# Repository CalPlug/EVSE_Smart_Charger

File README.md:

# EVSE Smart Charger

By: Andy Begey, Brandon Metcalf, Luis Contreras, Shermaine Dayot, Omair Farooqui, Krishan Solanki, Alex Ramirez, Emon Sahaba

Project Managers: Dr. Michael Klopfer, Prof. GP Li. 

University of California, Irvine - California Institute for Telecommunications and Information Technology (Calit2)  

---
Example ESP32-WROOM-32 application demo: operation of Electric Vehicle Supply Equipment (EVSE) Smart Charger that connects to the internet and MQTT server which will allow EV owners to control the charging schedules and monitor power consumption. Uses Smartenit MQTT format. 

Example Application note for ESP32-WROOM-32

Copyright © The Regents of the Univeristy of California, 2018-19

Released into the public domain.

# Installation
Required tasks needed for the project: 

1. Install Arduino ESP32 on Windows using this link: https://github.com/espressif/arduino-esp32/blob/master/docs/arduino-ide/windows.md

2. Open Arduino IDE. Click File->Open, then navigate to the following path:    
`EVSE code/Arduino/Current_Year_DevelopmentFirmware/EVChargerESP32RTOS`

3. Open `EVChargerESP32RTOS.ino`. The .ino file and the accompanying libraries should open in the IDE.

4. Use the library "esp32-hal-spi.h" for SPI. Can be obtained from doing the first task. 

5. Set the board to `ESP32 Dev Module`.

# Building 
After following the steps for installation, you can start by creating an account on your desired MQTT broker for testing purposes. It comes in many types of flavors, but our personal favorite and recommendation is CloudMQTT. Go to this link: https://www.cloudmqtt.com/. After you have created your account, prepare to gather the MQTT user, password, port and server because you need these in order to connect with your server. You also need to prepare your desired network name and password. It is very important to note that the ESP32 is itself an access point initally and that you would need to create its own server where the user can input their own MQTT server and Network for the ESP32 to connect to. In the initial stages of testing your software without implementing the ESP32 as its own access point, you would need to hardcode the information you have gathered in the beginning. 

# Background of Operation 

The Smart Charger initializes inputs and safety checks. After the safety check passes, it tries to connect to the wifi available. Then after being connected to the wifi it connects to the mqtt server. Initially the charger is in state A which means it is not plugged in. When it is plugged in but not charging, the charger is in state B. The wattmeter reads values such as Vrms, Irms, and active power. When it changes to state C which is at charging state, both relays will turn on. Pressing the button at certain amount of times will turn off the load, change the load, reset, and enter AP mode.  

# Usage
Smart Charger can be used to monitor the charging conditions of an electric vehicle. Online, an EV owner will be able to have control over the charger, for example they may ask for voltage levels and will be able to change the load going into the vehicle. It will be very useful in time as the number of electric vehicle users increase.  

## Connecting to WiFi

Upon first boot and after resets, the EVSE Smart Charger will start an access point (AP) to allow user to connect to a certain WiFI Access Point and MQTT broker.

1. On another device, connect to AP with SSID: `EVSESetup9B25B2`.
2. On a web browser, navigate to `192.168.10.10`.
3. Enter your valid WiFi and MQTT credentials on the form displayed. Then click 'Save.'
4. A success message should appear, the EVSE AP should disconnect, then the EVSE should connect to the WiFI network specified.

If there a failure, reset the EVSE networking information by pressing the reset button 11-12 times.

## MQTT Commands

The EVSE unit can be controlled remotely via MQTT commands.

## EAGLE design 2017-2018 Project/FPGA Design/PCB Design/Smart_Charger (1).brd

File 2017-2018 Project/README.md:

# EV_Smart_Charger
---
Example ESP32-WROOM-32 application demo: operation of Electric Vehicle Supply Equipment (EVSE) Smart Charger that connects to the internet and MQTT server which will allow EV owners to control the charging schedules and monitor power consumption. Uses Smartenit MQTT format. 

Example Application note for ESP32-WROOM-32

Created by Andy Begey, Brandon Metcalf, Luis Contreras, Shermaine Dayot 

Project Managers: Dr. Michael Klopfer, Prof. GP Li. 

University of California, Irvine - California Institute for Telecommunications and Information Technology (Calit2)  

Copyright (C) The Regents of the Univeristy of California, 2018

Released into the public domain.

# Installation
---
Required tasks needed for the project: 

1.) Install Arduino ESP32 on Windows using this link: https://github.com/espressif/arduino-esp32/blob/master/docs/arduino-ide/windows.md

2.) Install ADE7953-Wattmeter-master into Arduino library which can be found in the EVSE_Smart_Charger github. 
    Go to: EVSE code->Arduino->libraries->ADE7953-Wattmeter-master for ESP32.

3.) Use the library "esp32-hal-spi.h" for SPI. Can be obtained from doing the first task. 

# Building 
---
After following the steps for installation, you can start by creating an account on your desired MQTT broker for testing purposes. It comes in many types of flavors, but our personal favorite and recommendation is CloudMQTT. Go to this link: https://www.cloudmqtt.com/. After you have created your account, prepare to gather the mqtt user, password, port and server because you need these in order to connect with your server. You also need to prepare your desired network name and password. It is very important to note that the ESP32 is itself an access point initally and that you would need to create its own server where the user can input their own MQTT server and Network for the ESP32 to connect to. In the initial stages of testing your software without implementing the ESP32 as its own access point, you would need to hardcode the information you have gathered in the beginning. 

# Background of Operation 
---
The Smart Charger initializes inputs and safety checks. After the safety check passes, it tries to connect to the wifi available. Then after being connected to the wifi it connects to the mqtt server. Initially the charger is in state A which means it is not plugged in. When it is plugged in but not charging, the charger is in state B. The wattmeter reads values such as Vrms, Irms, and active power. When it changes to state C which is at charging state, both relays will turn on. Pressing the button at certain amount of times will turn off the load, change the load, reset, and enter AP mode.  

# Usage
---
Smart Charger can be used to monitor the charging conditions of an electric vehicle. Online, an EV owner will be able to have control over the charger, for example they may ask for voltage levels and will be able to change the load going into the vehicle. It will be very useful in time as the number of electric vehicle users increase.

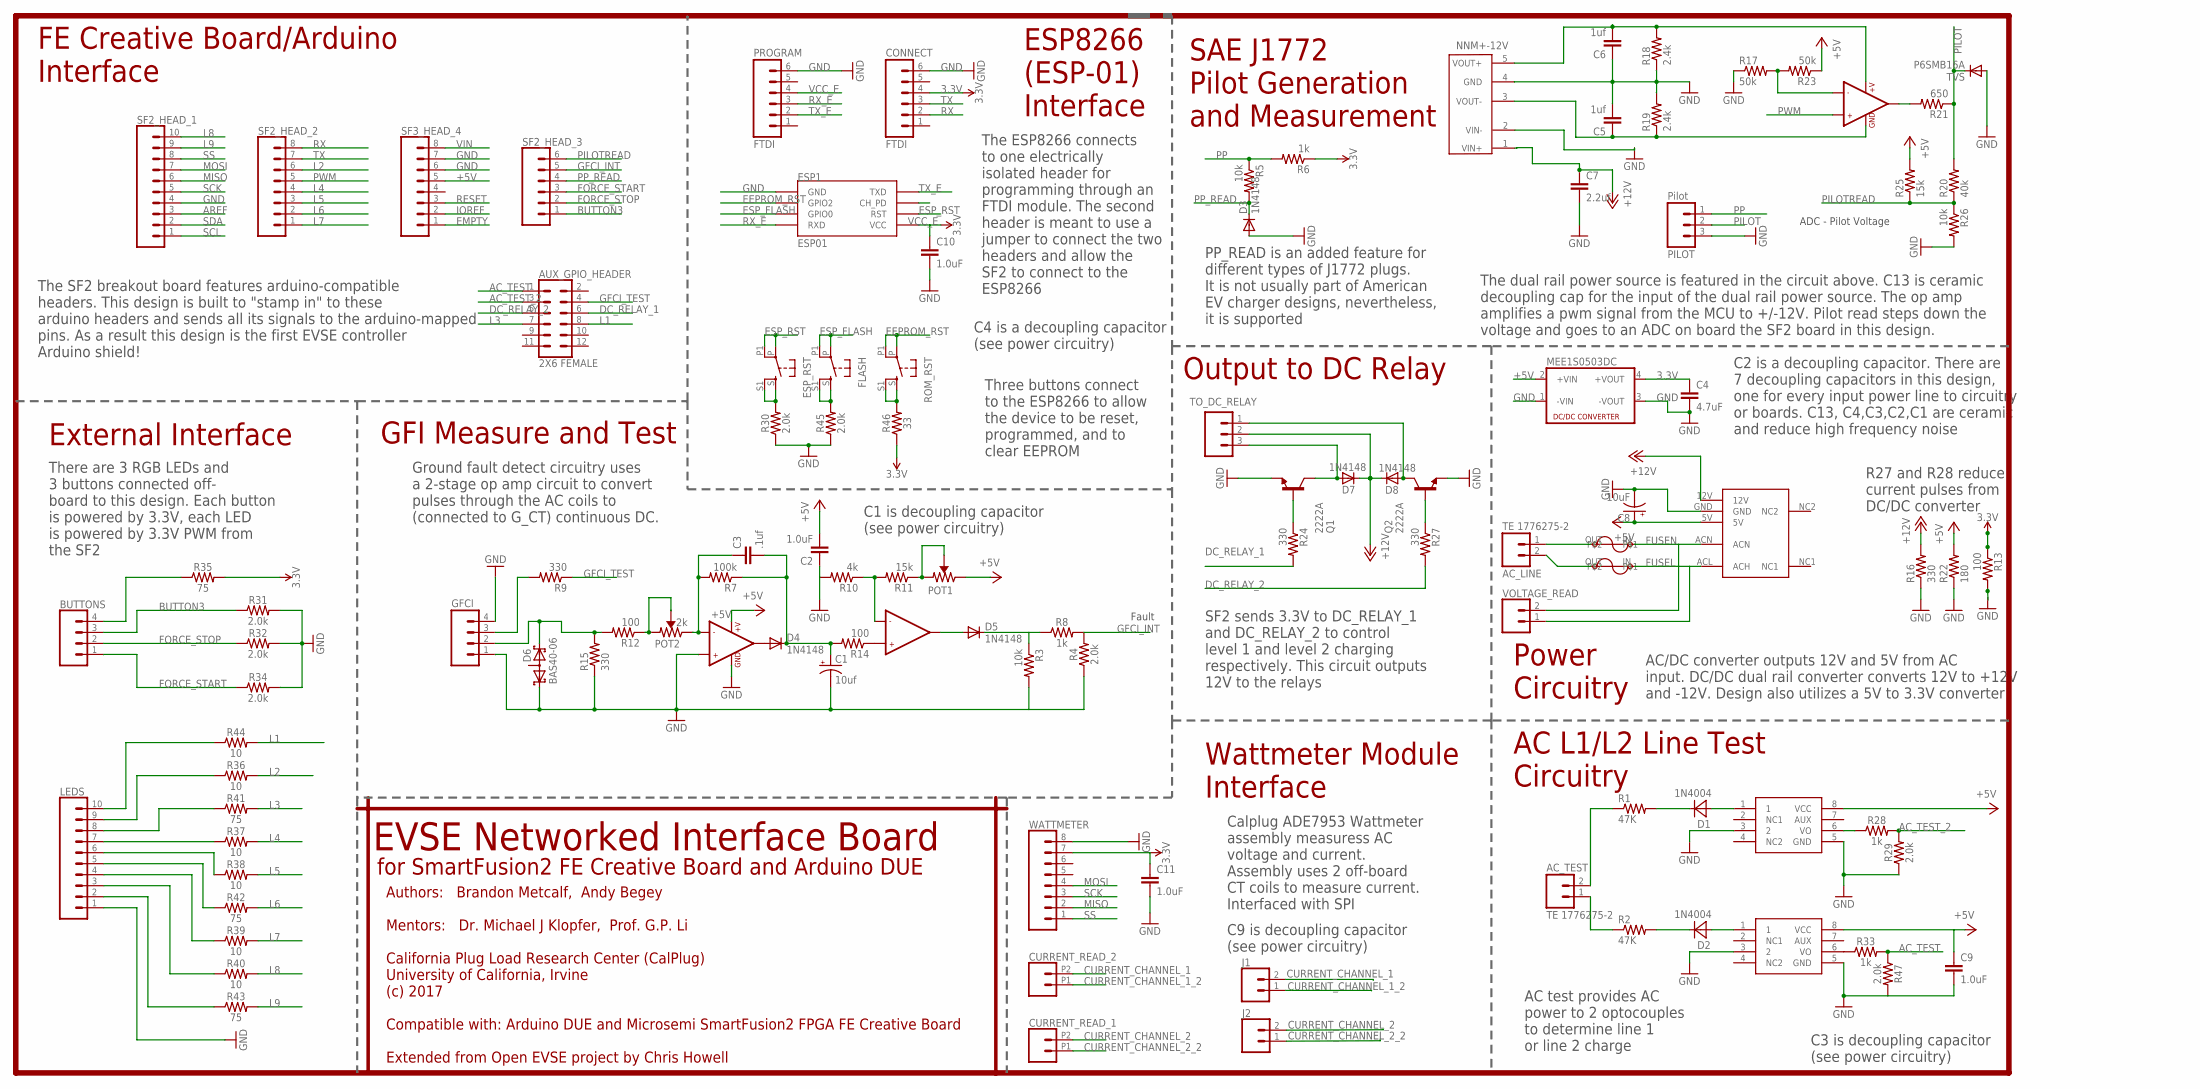
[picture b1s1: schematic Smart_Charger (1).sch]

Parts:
AC_LINE: TE 1776275-2; SCREWTERMINAL-3.5MM-2_LOCK
AC_TEST: TE 1776275-2; SCREWTERMINAL-3.5MM-2_LOCK
AUX_GPIO_HEADER: 2X6 FEMALE; 2X6
BUTTONS: CONN_04; 1X04
C1: 10uf; EIA3216
C2, C9, C10, C11: 1.0uF; 0805
C3: .1uf; 0805
C4: 4.7uF; 0805
C5, C6: 1uf; 0805
C7: 2.2uf; 0805
C8: 10uF; EIA3216
CONNECT: FTDI; 1X06
CURRENT_READ_1, CURRENT_READ_2: CONN_022.54MM_SCREWTERM; 1X02_2.54_SCREWTERM
D1, D2: 1N4004; SMA
D3, D4, D5, D7, D8: 1N4148; SOD123
D6: BAS40-06; SOT23
DC1: MPM-04E-1205
DC2: NNM+-12V; DIP_5
ESP1: ESP01
ESP_RST: 10-XX-4.5SMD; BT4.5X4.5
F1, F2: BEL1AFUSE; BELFUSE1A
FLASH: 10-XX-4.5SMD; BT4.5X4.5
GFCI: M04LOCK; 1X04_LOCK
IC1, IC2: MID400; DIP08
IC3, IC4: LMV358; SO08
J1, J2: CONN_02; 1X02
LEDS: CONN_10"; 1X10
MEE1S0503DC: NKE0305DC; 4SIL
PILOT: Pilot; SCREWTERMINAL-3.5MM-3_LOCK.007S
POT1: 10k; PV3G
POT2: 2k; PV3G
PROGRAM: FTDI; 1X06
Q1, Q2: 2222A; SOT23
R1, R2: 47K; AXIAL-0.4
R3, R5, R26: 10k; 0603-RES
R4, R29, R30, R31, R32, R34, R45, R47: 2.0k; 0603
R6: 1k; 0603-RES
R7: 100k; 0805
R8, R28, R33: 1k; 0603
R9, R15, R24, R27: 330; 0603-RES
R10: 4k; 0603-RES
R11: 15k; 0805
R12, R13, R14: 100; 0603-RES
R16: 330; R0603
R17, R23: 50k; 0805
R18, R19: 2.4k; 0603-RES
R20: 40k; 0603-RES
R21: 650; 0603-RES
R22: 180; R0603
R25: 15k; 0603-RES
R35, R41, R42, R43: 75; 0603
R36, R37, R38, R39, R40, R44: 10; 0603
R46: 33; 0603
ROM_RST: 10-XX-4.5SMD; BT4.5X4.5
SF2_HEAD_1: CONN_10"; 1X10
SF2_HEAD_2, SF3_HEAD_4: CONN_08"; 1X08
SF2_HEAD_3: CONN_06SILK_FEMALE_PTH; 1X06
TO_DC_RELAY: M03SCREW_LOCK; SCREWTERMINAL-3.5MM-3_LOCK.007S
TVS: P6SMB16A; SMB
VOLTAGE_READ: CONN_025MM; SCREWTERMINAL-5MM-2
WATTMETER: CONN_08"; 1X08

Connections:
3.3V: C4.1, C11.1, CONNECT.4, MEE1S0503DC.4 (+VOUT), R6.1, R13.1, R35.2, R46.1, WATTMETER.7
12V: C6.2, DC2.5 (VOUT+), IC4.8 (+V), R18.2
+5V: C2.2, C8.+, C9.1, DC1.5V, IC1.8 (VCC), IC2.8 (VCC), IC3.8 (+V), MEE1S0503DC.2 (+VIN), POT1.P$3 (CW), R22.2, R23.1, R25.2, SF3_HEAD_4.5
+12V: C7.1, D7.C, D8.C, DC1.12V, DC2.1 (VIN+), R16.2, TO_DC_RELAY.2
-12V: C5.1, DC2.3 (VOUT-), IC4.4 (GND), R19.1
AC_TEST: AUX_GPIO_HEADER.1, R33.2, R47.1
AC_TEST_2: AUX_GPIO_HEADER.3, R28.2, R29.2
AREF: SF2_HEAD_1.3
BUTTON3: BUTTONS.3, R31.1, SF2_HEAD_3.1
CURRENT_CHANNEL_1: CURRENT_READ_2.P2 (2), J1.2
CURRENT_CHANNEL_1_2: CURRENT_READ_2.P1 (1), J1.1
CURRENT_CHANNEL_2: CURRENT_READ_1.P2 (2), J2.2
CURRENT_CHANNEL_2_2: CURRENT_READ_1.P1 (1), J2.1
DC_RELAY_1: AUX_GPIO_HEADER.6, R24.2
DC_RELAY_2: AUX_GPIO_HEADER.5, R27.2
EEPROM_RST: ESP1.GPIO2, ROM_RST.P, ROM_RST.P1
EMPTY: SF3_HEAD_4.1
ESP_FLASH: ESP1.GPIO0, FLASH.P, FLASH.P1
ESP_RST: ESP1.RST, ESP_RST.P, ESP_RST.P1
FORCE_START: BUTTONS.1, R34.1, SF2_HEAD_3.3
FORCE_STOP: BUTTONS.2, R32.1, SF2_HEAD_3.2
FUSEL: DC1.ACL (ACH), F2.IN, VOLTAGE_READ.1
FUSEN: DC1.ACN, F1.IN, VOLTAGE_READ.2
GFCI_INT: R4.2, R8.2, SF2_HEAD_3.5
GFCI_TEST: AUX_GPIO_HEADER.4, R9.1
GND: C1.C (-), C2.1, C4.2, C5.2, C6.1, C7.2, C8.-, C9.2, C10.2, C11.2, CONNECT.6, D3.A, D6.1 (K1), DC1.GND, DC2.2 (VIN-), DC2.4 (GND), ESP1.GND, GFCI.1, GFCI.4, IC1.3 (2), IC1.5 (GND), IC2.3 (2), IC2.5 (GND), IC3.3 (+IN1), IC3.4 (GND), LEDS.1, MEE1S0503DC.1 (-VIN), MEE1S0503DC.3 (-VOUT), PILOT.3, PROGRAM.6, Q1.2 (E), Q2.2 (E), R3.2, R4.1, R10.2, R13.2, R15.1, R16.1, R17.1, R18.1, R19.2, R22.1, R26.2, R29.1, R30.1, R31.2, R32.2, R34.2, R45.1, R47.2, SF2_HEAD_1.4, SF3_HEAD_4.6, SF3_HEAD_4.7, TVS.A
IOREF: SF3_HEAD_4.2
L1: AUX_GPIO_HEADER.8, R44.2
L2: R36.2, SF2_HEAD_2.6
L3: AUX_GPIO_HEADER.7, R41.2
L4: R37.2, SF2_HEAD_2.4
L5: R38.2, SF2_HEAD_2.3
L6: R42.2, SF2_HEAD_2.2
L7: R39.2, SF2_HEAD_2.1
L8: R40.2, SF2_HEAD_1.10
L9: R43.2, SF2_HEAD_1.9
MISO: SF2_HEAD_1.6, WATTMETER.2
MOSI: SF2_HEAD_1.7, WATTMETER.4
unnamed: D8.A, Q2.3 (C), TO_DC_RELAY.1
unnamed: Q2.1 (B), R27.1
unnamed: IC2.6 (VO), R28.1
unnamed: D5.C, R3.1, R8.1
unnamed: POT2.P$1 (CCW), POT2.P$2 (WIPER), R12.1
unnamed: D7.A, Q1.3 (C), TO_DC_RELAY.3
unnamed: POT1.P$1 (CCW), POT1.P$2 (WIPER), R11.1
unnamed: C3.1, IC3.2 (-IN1), POT2.P$3 (CW), R7.2
unnamed: D1.C, R1.P$2 (2)
unnamed: IC4.2 (-IN1), R17.2, R23.2
unnamed: IC4.1 (OUT1), R21.2
unnamed: AC_LINE.2, F2.OUT
unnamed: AC_LINE.1, F1.OUT
unnamed: LEDS.10, R44.1
unnamed: LEDS.9, R36.1
unnamed: LEDS.8, R41.1
unnamed: AC_TEST.2, R1.P$1 (1)
unnamed: LEDS.7, R37.1
unnamed: D1.A, IC2.1
unnamed: D6.2 (K2), GFCI.2, R12.2, R15.2
unnamed: D4.A, IC3.1 (OUT1)
unnamed: GFCI.3, R9.2
unnamed: C1.A (+), C3.2, D4.C, R7.1, R14.2
unnamed: IC3.6 (-IN2), R10.1, R11.2
unnamed: D5.A, IC3.7 (OUT2)
unnamed: IC3.5 (+IN2), R14.1
unnamed: D2.C, R2.P$2 (2)
unnamed: D2.A, IC1.1
unnamed: AC_TEST.1, R2.P$1 (1)
unnamed: Q1.1 (B), R24.1
unnamed: LEDS.6, R38.1
unnamed: LEDS.5, R42.1
unnamed: LEDS.4, R39.1
unnamed: LEDS.2, R43.1
unnamed: LEDS.3, R40.1
unnamed: R46.2, ROM_RST.S, ROM_RST.S1
unnamed: FLASH.S, FLASH.S1, R45.2
unnamed: IC1.6 (VO), R33.1
unnamed: ESP_RST.S, ESP_RST.S1, R30.2
unnamed: BUTTONS.4, R35.1
NC3: WATTMETER.8
PILOT: PILOT.2, R20.2, R21.1, TVS.C
PILOTREAD: R20.1, R25.1, R26.1, SF2_HEAD_3.6
PP: PILOT.1, R5.1, R6.2
PP_READ: D3.C, R5.2, SF2_HEAD_3.4
PWM: IC4.3 (+IN1), SF2_HEAD_2.5
RESET: SF3_HEAD_4.3
RX: CONNECT.2, SF2_HEAD_2.8
RX_E: ESP1.RX (RXD), PROGRAM.3
SCK: SF2_HEAD_1.5, WATTMETER.3
SCL: SF2_HEAD_1.1
SDA: SF2_HEAD_1.2
SS: SF2_HEAD_1.8, WATTMETER.1
TX: CONNECT.3, SF2_HEAD_2.7
TX_E: ESP1.TX (TXD), PROGRAM.2
VCC_E: C10.1, ESP1.VCC, PROGRAM.4
VIN: SF3_HEAD_4.8

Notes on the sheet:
SAE J1772 Pilot Generation and Measurement
ADC - Pilot Voltage
Fault
Ground fault detect circuitry uses a 2-stage op amp circuit to convert pulses through the AC coils to (connected to G_CT) continuous DC.
FE Creative Board/Arduino Interface
External Interface
GFI Measure and Test
ESP8266 (ESP-01) Interface
Wattmeter Module Interface
Output to DC Relay
Power Circuitry
AC L1/L2 Line Test Circuitry
C1 is decoupling capacitor (see power circuitry)
There are 3 RGB LEDs and 3 buttons connected off- board to this design. Each button is powered by 3.3V, each LED is powered by 3.3V PWM from the SF2
Calplug ADE7953 Wattmeter assembly measuress AC voltage and current. Assembly uses 2 off-board CT coils to measure current. Interfaced with SPI
C9 is decoupling capacitor (see power circuitry)
C3 is decoupling capacitor (see power circuitry)
AC test provides AC power to 2 optocouples to determine line 1 or line 2 charge
C2 is a decoupling capacitor. There are 7 decoupling capacitors in this design, one for every input power line to circuitry or boards. C13, C4,C3,C2,C1 are ceramic and reduce high frequency noise
R27 and R28 reduce current pulses from DC/DC converter
AC/DC converter outputs 12V and 5V from AC input. DC/DC dual rail converter converts 12V to +12V and -12V. Design also utilizes a 5V to 3.3V converter
PP_READ is an added feature for different types of J1772 plugs. It is not usually part of American EV charger designs, nevertheless, it is supported
The dual rail power source is featured in the circuit above. C13 is ceramic decoupling cap for the input of the dual rail power source. The op amp amplifies a pwm signal from the MCU to +/-12V. Pilot read steps down the voltage and goes to an ADC on board the SF2 board in this design.
The ESP8266 connects to one electrically isolated header for programming through an FTDI module. The second header is meant to use a jumper to connect the two headers and allow the SF2 to connect to the ESP8266
Three buttons connect to the ESP8266 to allow the device to be reset, programmed, and to clear EEPROM
C4 is a decoupling capacitor (see power circuitry)
SF2 sends 3.3V to DC_RELAY_1 and DC_RELAY_2 to control level 1 and level 2 charging respectively. This circuit outputs 12V to the relays
The SF2 breakout board features arduino-compatible headers. This design is built to "stamp in" to these arduino headers and sends all its signals to the arduino-mapped pins. As a result this design is the first EVSE controller Arduino shield!
EVSE Networked Interface Board
Authors: Brandon Metcalf, Andy Begey Mentors: Dr. Michael J Klopfer, Prof. G.P. Li California Plug Load Research Center (CalPlug) University of California, Irvine (c) 2017 Compatible with: Arduino DUE and Microsemi SmartFusion2 FPGA FE Creative Board Extended from Open EVSE project by Chris Howell
for SmartFusion2 FE Creative Board and Arduino DUE

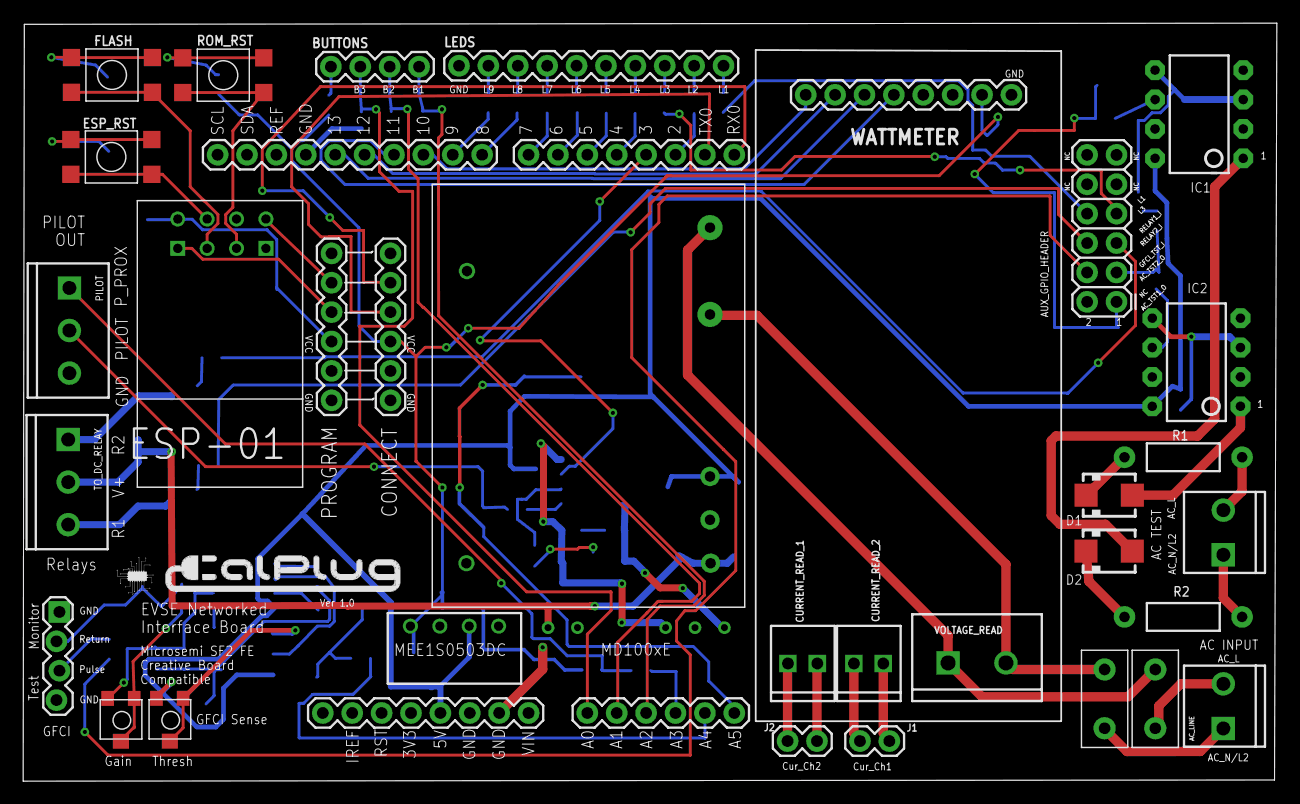
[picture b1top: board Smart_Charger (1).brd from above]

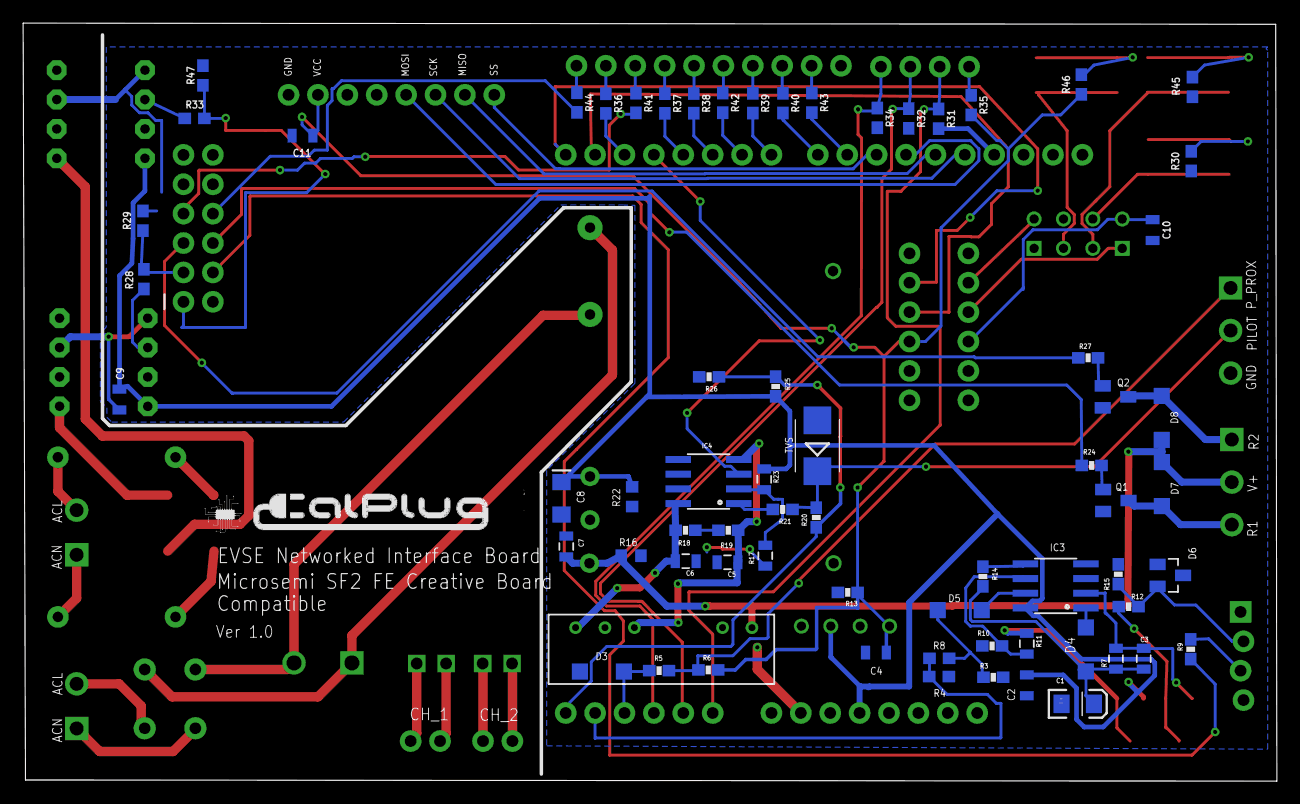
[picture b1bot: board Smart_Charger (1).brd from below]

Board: 2 copper layers, 108.3 x 65.5 mm, 104 parts (68 on the bottom side), 87 nets.

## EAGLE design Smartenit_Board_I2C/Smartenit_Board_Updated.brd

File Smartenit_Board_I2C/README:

This is an updated board and schematics to a more readable format and includes a header for I2C.

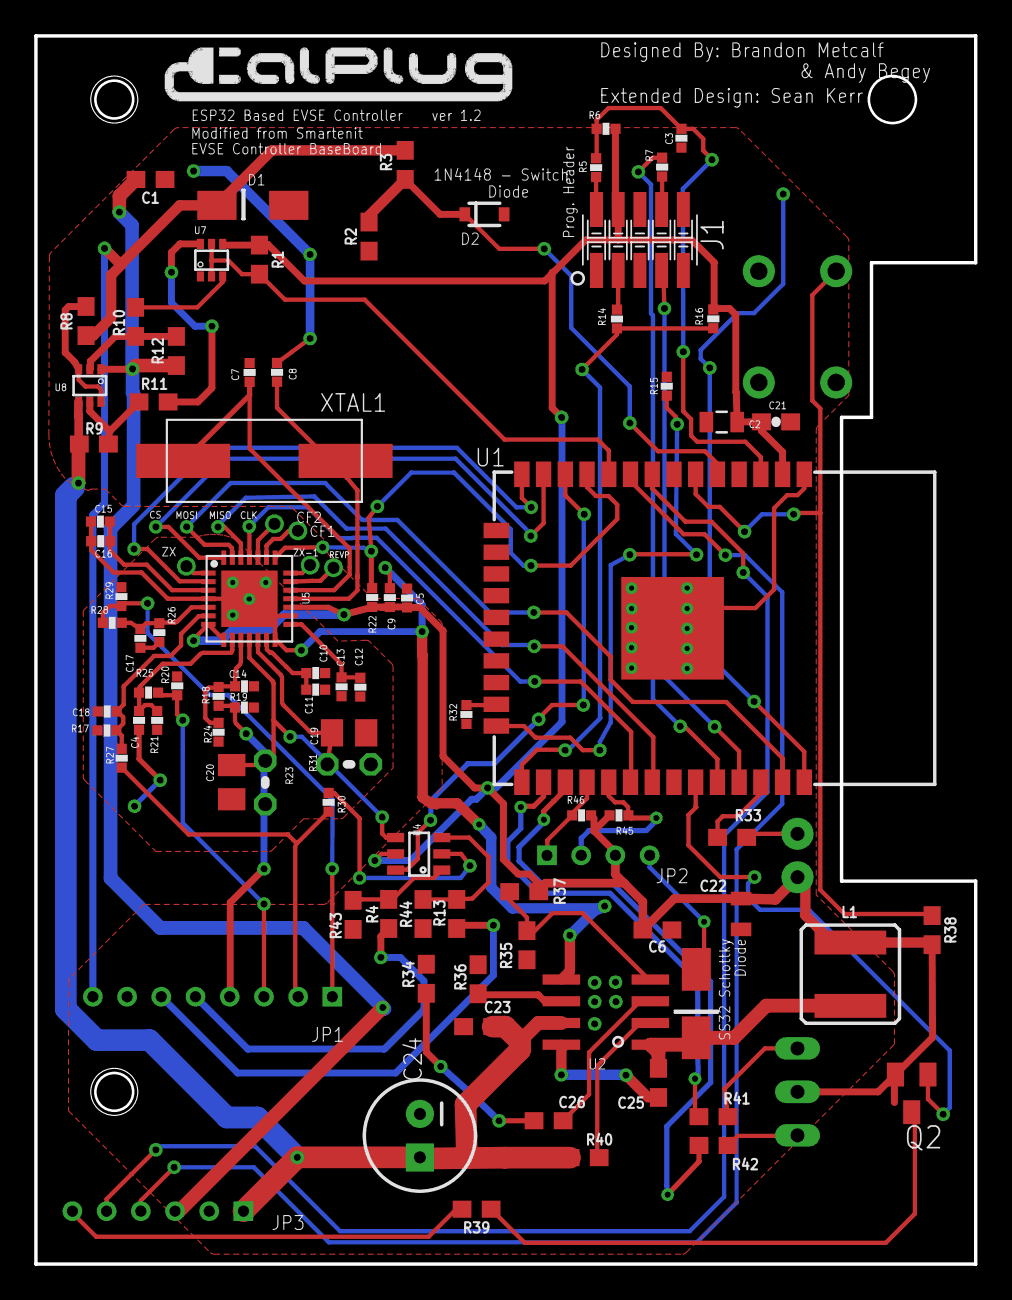
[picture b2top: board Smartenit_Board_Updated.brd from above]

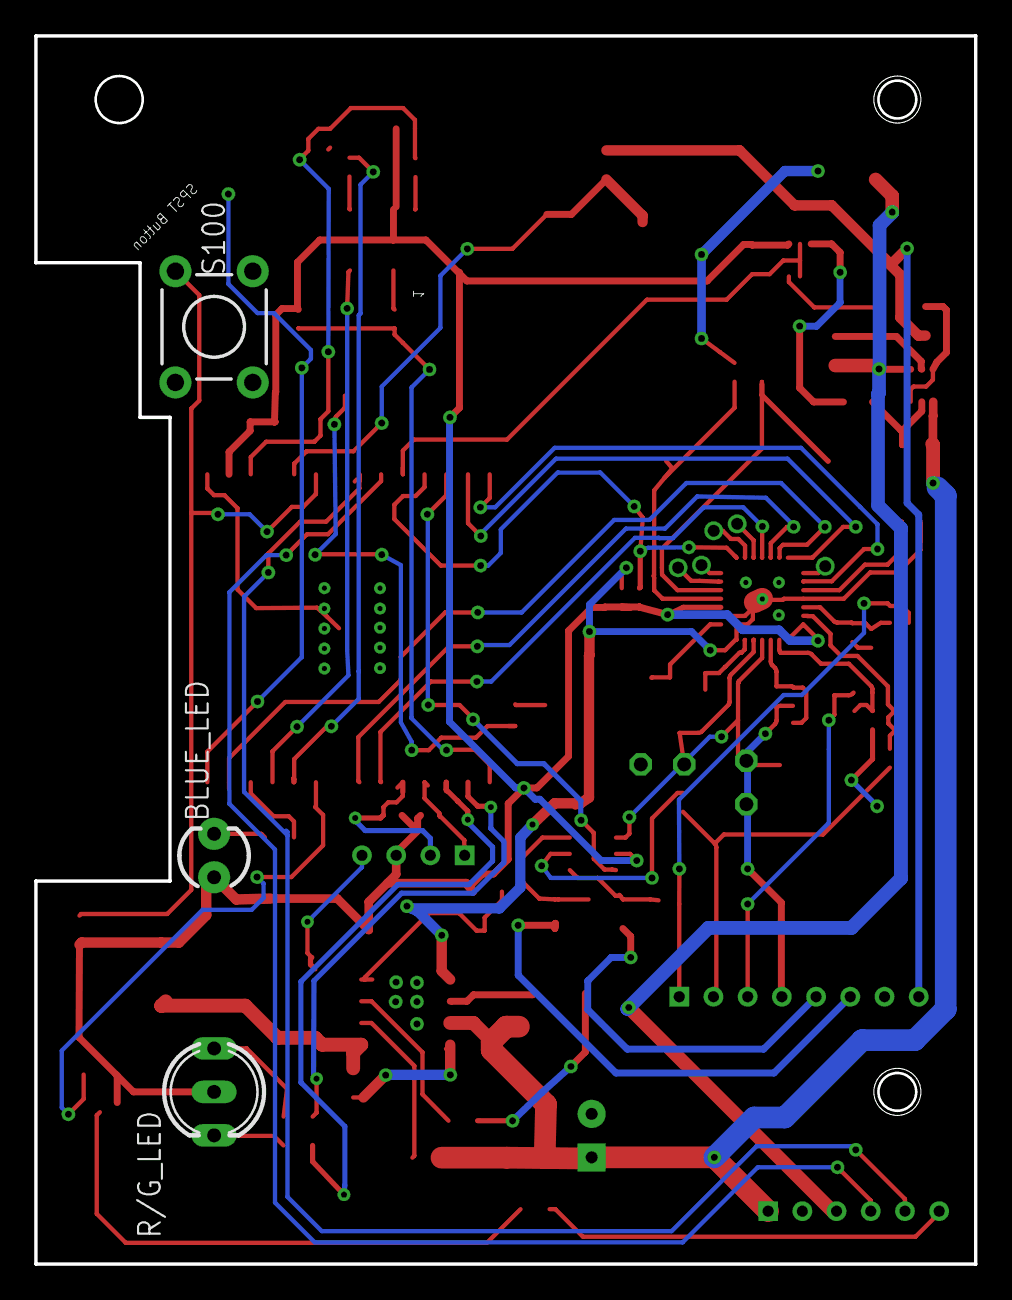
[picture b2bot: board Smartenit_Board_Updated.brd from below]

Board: 2 copper layers, 54.9 x 71.8 mm, 91 parts (3 on the bottom side), 69 nets.

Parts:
BLUE_LED: LED3MM
C1, C6, C23, C25, C26: 680pF; 0603
C2: 10uF/6.3V; 0805
C3, C9, C10, C13, C16: 0.1 uF; 0402-CAP
C4, C14, C17, C18: 33 nF; 0402-CAP
C5: 10 uF/10V; 0402-CAP
C7, C8: 20p; 0402-CAP
C11, C12, C15: 4.7 μF; 0402-CAP
C19, C20: 33 nF; C0805K
C21: 0.1 uF; 0603-CAP
C22: 10uF; 0805
C24: 100uF; CPOL-RADIAL-100UF-25V
D1: P6SMB16A; D014AC
D2: SOD-323
D3: SS32_DIODE; D0-214AB
J1: 2X5CONNECTOR1.27MM; 1296-10
JP1: 2MM_CONN8; CONN82MM
JP2: 2MM_CONN4; CONN4_2MM
JP3: 2MM_CONN6; CONN6_2MM
L1: 47µH/±30%/750mA; CR54
Q2: SOT23
R1, R2, R3, R8, R9, R10, R11, R12, R34, R35, R36, R37, R39, R40: 100k; 0603
R4, R13, R43, R44: 1k; 0603
R5, R7, R14, R15: 470; 0402-RES
R6, R16, R32: 12k; 0402-RES
R17, R21, R24, R26: 1k; 0402-RES
R18, R25, R27, R28: 9.1k; 0402-RES
R19, R20, R29, R30: 51; 0402-RES
R22: 10k; 0402-RES
R23, R31: 1k; 0204V
R33, R41, R42: 10k; 0603
R38: 4.7k; 0603
R45, R46: 4.7k; 0402-RES
R/G_LED: DUOLED-A-5MM
S100: SWITCH-MOMENTARY-2PTH; TACTILE-PTH
U1: ESP-WROOM-32
U2: MP1584; SOIC8
U4: SN74LVC1G3157; DBV-6
U5: ADE7953; 28-WFQFN
U7, U8: DMC3400SSDW; SOT363
XTAL1: QUARTZ_3.58M_2PIN; HC-49S

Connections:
3.3V: BLUE_LED.A, C2.1, C5.2, C6.2, C9.2, C21.1, C22.1, J1.4, JP2.3, L1.P$1, Q2.2, R1.1, R6.2, R16.2, R22.1, R37.2, R38.2, R45.2, R46.2, R/G_LED.A, U1.2, U4.5, U5.7, U5.8, U5.17, U7.4
12V: C23.2, C24.1, JP3.6, R9.1, R40.2, U2.7, U8.4
-12V: C1.2, JP3.4, R12.1, U8.1
AGND: C4.1, C10.2, C11.2, C12.1, C13.1, C14.2, C17.1, C18.2, C19.2, C20.2, R17.2, R19.2, R20.1, R21.1, R23.2, R24.2, R26.1, R29.1, R30.2, R31.2, U4.2, U5.16
BLUE_LED: R33.1, U1.36
BUTTON: R38.1, S100.3, U1.6
CS: U1.13, U5.28
DGND: C1.1, C2.2, C3.1, C5.1, C6.1, C7.1, C8.1, C9.1, C15.1, C16.1, C21.2, C22.2, C23.1, C24.2, D1.P, D2.2, D3.P, J1.10, JP2.4, JP3.5, R2.1, R15.1, R32.1, R34.1, R35.1, R36.1, R43.2, R44.1, S100.1, U1.1, U1.15, U1.38, U1.GND, U2.5, U5.4, U5.14, U5.PAD, U7.1
DIO5: R22.2, U1.11, U5.22
FRGGN: R32.2, U1.23
GPIO0: R14.1, R16.1, U1.25
GPIO2: R15.2, U1.24
GREEN_LED: R41.1, U1.26
IAN: JP1.2, R27.1, R30.1
IAP: JP1.1, R28.1, R29.2
IBN: JP1.4, R18.1, R19.1
IBP: JP1.3, R20.2, R25.1
LNV1: JP1.5, R4.1
LNV2: JP1.6, R13.1
MPLEX: U1.12, U4.6
unnamed: C7.2, U5.19, XTAL1.1
unnamed: C8.2, U5.18, XTAL1.2
unnamed: C20.1, R23.1, U4.4, U5.11
unnamed: R36.2, U2.6
unnamed: C4.2, R21.2, R25.2, U5.9
unnamed: C10.1, C11.1, U5.13
unnamed: C12.2, C13.2, U5.15
unnamed: R4.2, R43.1, U4.1
unnamed: C14.1, R18.2, R24.1, U5.10
unnamed: C15.2, C16.2, U5.3
unnamed: R13.2, R44.2, U4.3
unnamed: R40.1, U2.2
unnamed: C26.2, U2.3
unnamed: C26.1, R34.2
unnamed: C25.2, D3.N, L1.P$2, U2.1
unnamed: R35.2, R37.1, U2.4
unnamed: Q2.3, R39.1
unnamed: BLUE_LED.K, R33.2
unnamed: C25.1, U2.8
unnamed: R9.2, R11.2, U8.5
unnamed: C17.2, R26.2, R28.2, U5.5
unnamed: R41.2, R/G_LED.CX
unnamed: R42.2, R/G_LED.CR
unnamed: C18.1, R17.1, R27.2, U5.6
unnamed: R10.1, U7.3
unnamed: R10.2, R12.2, U8.2
unnamed: R11.1, U7.6
unnamed: R8.1, U8.3, U8.6
unnamed: JP3.1, R39.2
unnamed: J1.3, R14.2
unnamed: J1.2, R5.1
unnamed: J1.8, R7.1
NRST: C3.2, R5.2, R6.1, U1.3
PILOT: D1.N, JP1.8, R3.2, R8.2
PILOT_GEN: R1.2, U1.10, U7.2, U7.5
PILOT_READ: D2.1, R2.2, R3.1, U1.5
RED_LED: R42.1, U1.27
RELAY1: JP3.2, U1.8
RELAY2: JP3.3, U1.9
RELAY_EN: Q2.1, U1.33
RESET_ISO: U1.14, U5.2
RXD0: R7.2, U1.34
SCL: JP2.1, R46.1, U1.28
SDA: JP2.2, R45.1, U1.29
SPIMISO: U1.31, U5.26
SPIMOSI: U1.37, U5.27
SPISCLK: U1.30, U5.25
TXD0: J1.7, U1.35
V2P: C19.1, R31.1, U5.12

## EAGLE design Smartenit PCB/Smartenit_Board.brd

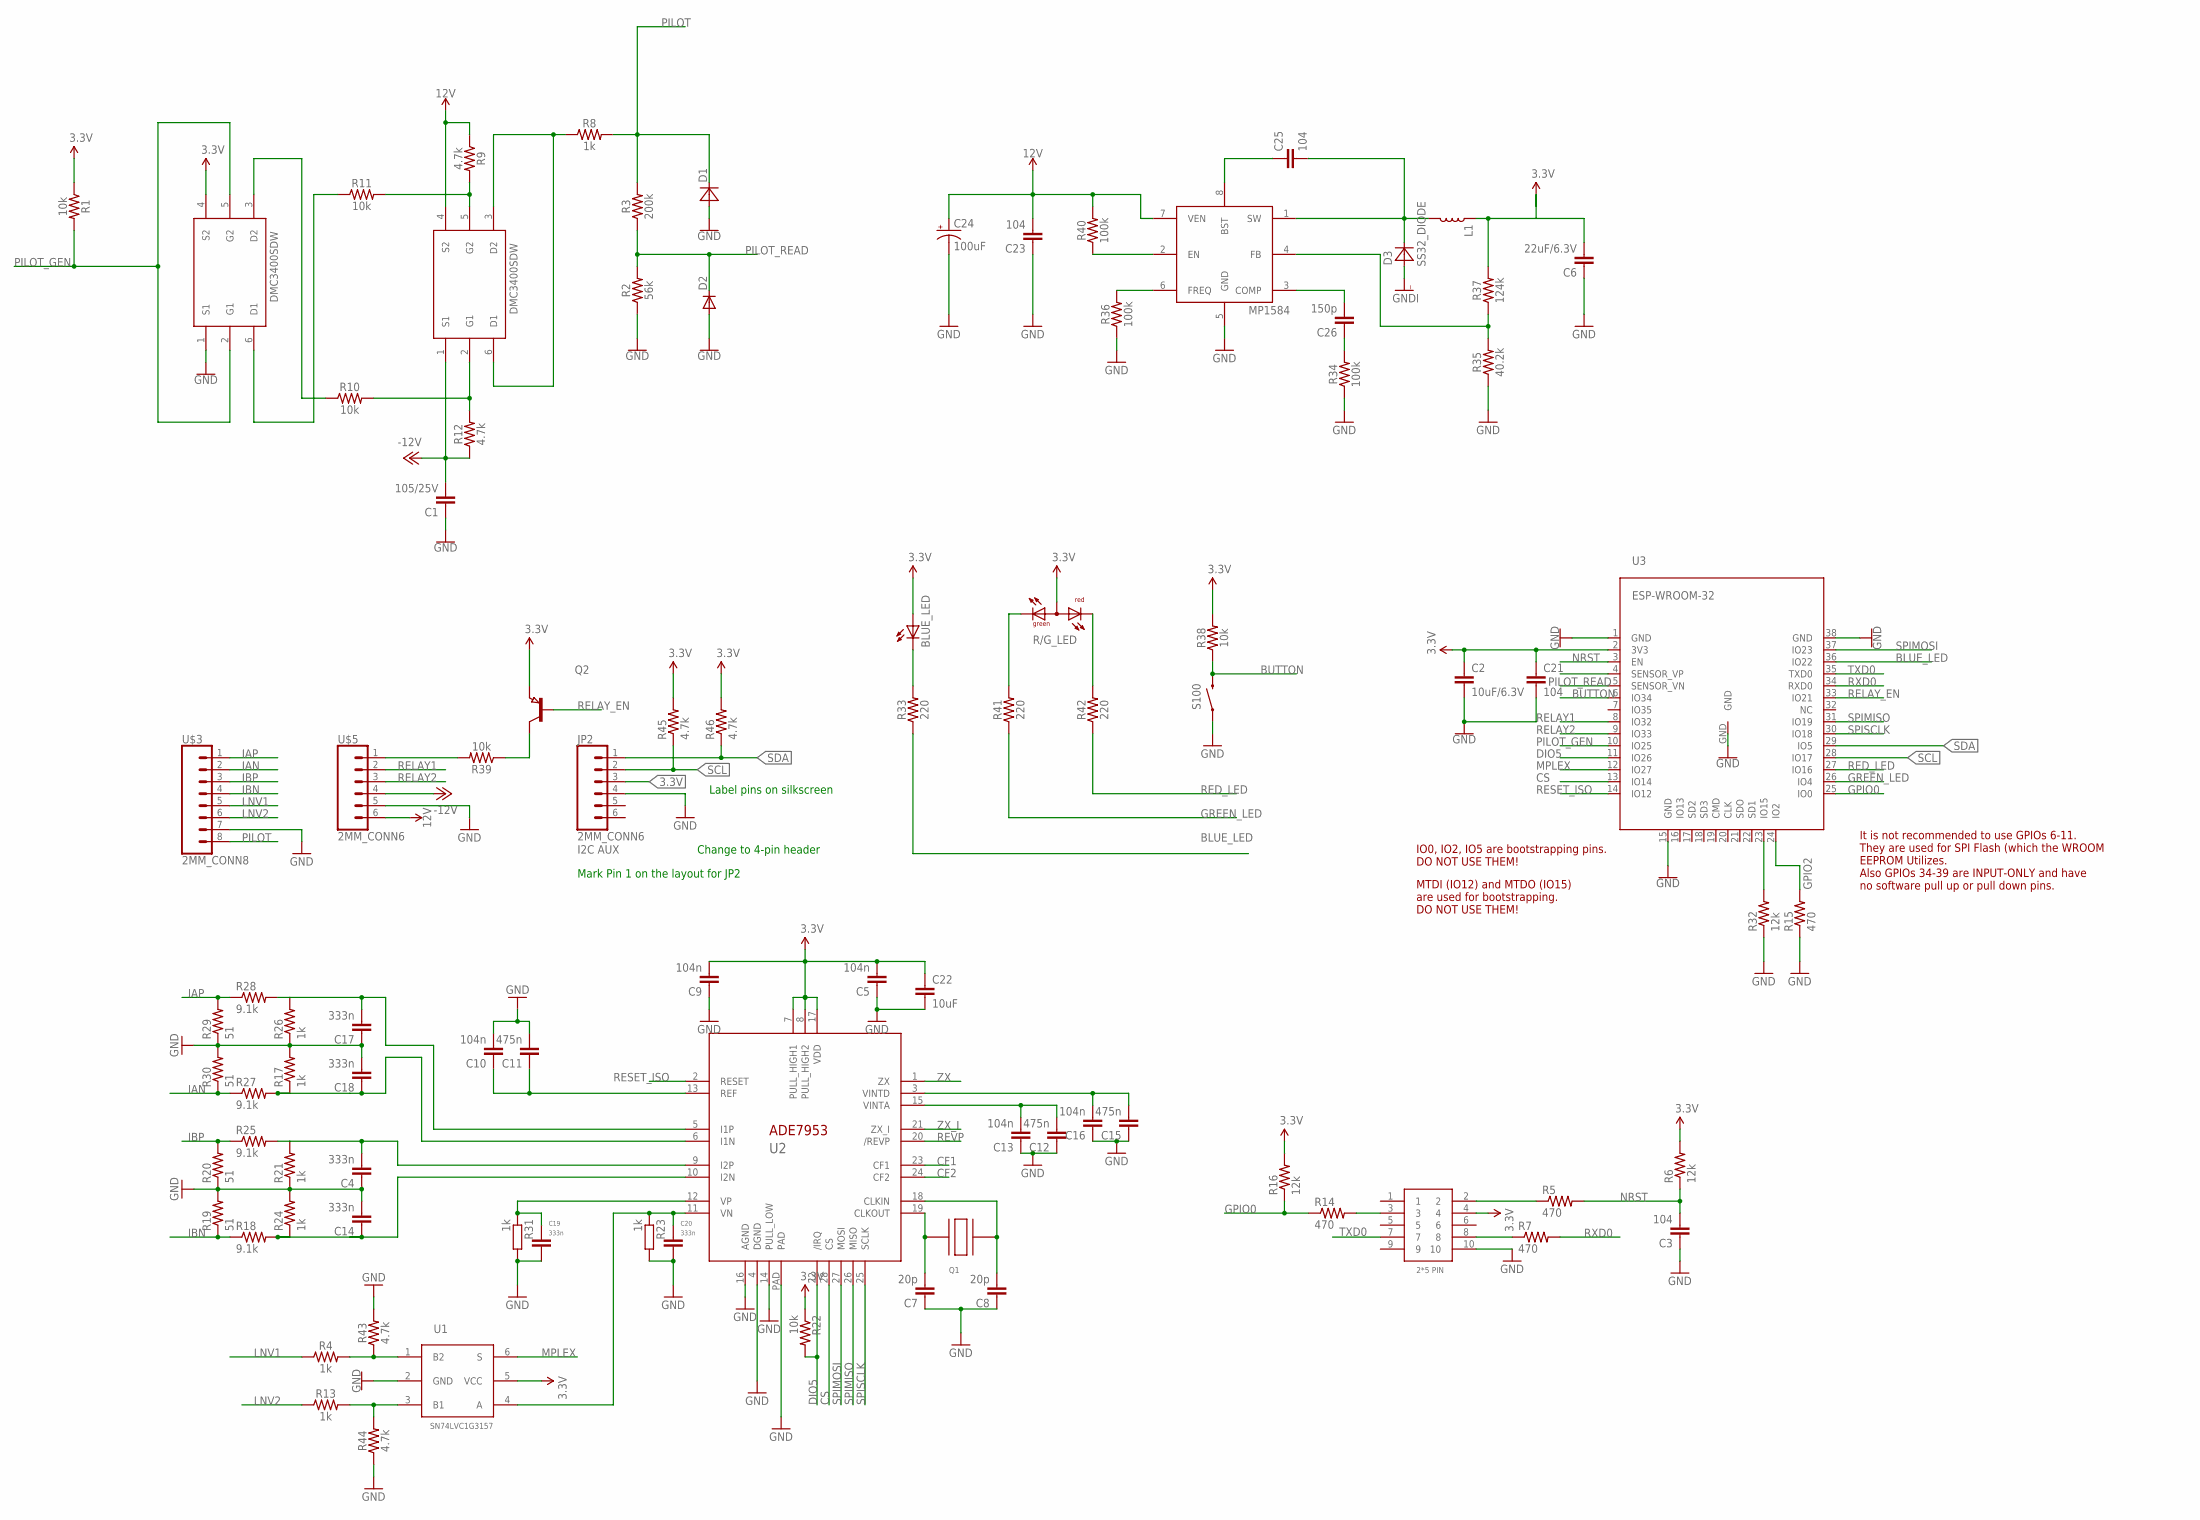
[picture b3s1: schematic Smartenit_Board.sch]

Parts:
BLUE_LED: LED3MM
C1: 105/25V; 0603
C2: 10uF/6.3V; 0805
C3: 104; 0402-CAP
C4, C14, C17, C18: 333n; 0402-CAP
C5, C9, C10, C13, C16: 104n; 0402-CAP
C6: 22uF/6.3V; 0603
C7, C8: 20p; 0402-CAP
C11, C12, C15: 475n; 0402-CAP
C19, C20: 333n; C0805K
C21: 104; 0603-CAP
C22: 10uF; 0805
C23, C25: 104; 0603
C24: 100uF; CPOL-RADIAL-100UF-25V
C26: 150p; 0603
D1: P6SMB16A; D014AC
D2: DIODESOD; SOD-323
D3: SS32_DIODE; D0-214AB
J1: 2X5CONNECTOR1.27MM; 1296-10
JP2: 2MM_CONN6; CONN6_2MM
L1: 47µH/±30%/750mA; CR54
Q1: QUARTZ_3.58M_2PIN; HC-49S
Q2: PNP-TRANSISTOR_SOT23; SOT23
R1, R10, R11, R38, R39: 10k; 0603
R2: 56k; 0603
R3: 200k; 0603
R4, R8, R13: 1k; 0603
R5, R7, R14, R15: 470; 0402-RES
R6, R16, R32: 12k; 0402-RES
R9, R12, R43, R44: 4.7k; 0603
R17, R21, R24, R26: 1k; 0402-RES
R18, R25, R27, R28: 9.1k; 0402-RES
R19, R20, R29, R30: 51; 0402-RES
R22: 10k; 0402-RES
R23, R31: 1k; C0805K@1
R33, R41, R42: 220; 0603
R34, R36, R40: 100k; 0603
R35: 40.2k; 0603
R37: 124k; 0603
R45, R46: 4.7k; 0402-RES
R/G_LED: DUOLED-RG-A; DUOLED-A-5MM
S100: SWITCH-MOMENTARY-2PTH; TACTILE-PTH
U1: SN74LVC1G3157; DBV-6
U2: ADE7953; 28-WFQFN
U3: ESP-WROOM-32
U$1, U$2: DMC3400SSDW; SOT363
U$3: 2MM_CONN8; CONN82MM
U$4: MP1584; SOIC8
U$5: 2MM_CONN6; CONN6_2MM

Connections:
3.3V: BLUE_LED.A, C2.1, C5.2, C6.2, C9.2, C21.1, C22.1, J1.4, JP2.3 (PIN3), L1.P$1 (1), Q2.2 (E), R1.1, R6.2, R16.2, R22.1, R37.2, R38.2, R45.2, R46.2, R/G_LED.A, U1.5 (VCC), U2.7 (PULL_HIGH1), U2.8 (PULL_HIGH2), U2.17 (VDD), U3.2 (3V3), U$1.4 (S2)
12V: C23.2, C24.1 (+), R9.1, R40.2, U$2.4 (S2), U$4.7 (VEN), U$5.6 (PIN6)
-12V: C1.2, R12.1, U$2.1 (S1), U$5.4 (PIN4)
AGND: C4.1, C10.2, C11.2, C12.1, C13.1, C14.2, C17.1, C18.2, C19.2, C20.2, R17.2, R19.2, R20.1, R21.1, R23.2, R24.2, R26.1, R29.1, R30.2, R31.2, U1.2 (GND), U2.16 (AGND), U$3.7
BLUE_LED: R33.1, U3.36 (IO22)
BUTTON: R38.1, S100.3 (2), U3.6 (IO34)
CF1: U2.23 (CF1)
CF2: U2.24 (CF2)
CS: U2.28 (CS), U3.13 (IO14)
DGND: C1.1, C2.2, C3.1, C5.1, C6.1, C7.1, C8.1, C9.1, C15.1, C16.1, C21.2, C22.2, C23.1, C24.2 (-), D1.P, D2.2 (A), D3.P, J1.10, R2.1, R15.1, R32.1, R34.1, R35.1, R36.1, R43.2, R44.1, S100.1, U2.4 (DGND), U2.14 (PULL_LOW), U2.PAD, U3.1 (GND), U3.15 (GND), U3.38 (GND), U3.GND, U$1.1 (S1), U$4.5 (GND), U$5.5 (PIN5)
DIO5: R22.2, U2.22 (/IRQ), U3.11 (IO26)
FRGGN: R32.2, U3.23 (IO15)
GND: JP2.4 (PIN4)
GPIO0: R14.1, R16.1, U3.25 (IO0)
GPIO2: R15.2, U3.24 (IO2)
GREEN_LED: R41.1, U3.26 (IO4)
IAN: R27.1, R30.1, U$3.2
IAP: R28.1, R29.2, U$3.1
IBN: R18.1, R19.1, U$3.4
IBP: R20.2, R25.1, U$3.3
LNV1: R4.1, U$3.5
LNV2: R13.1, U$3.6
MPLEX: U1.6 (S), U3.12 (IO27)
unnamed: C7.2, Q1.1, U2.19 (CLKOUT)
unnamed: C8.2, Q1.2, U2.18 (CLKIN)
unnamed: C20.1, R23.1, U1.4 (A), U2.11 (VN)
unnamed: R36.2, U$4.6 (FREQ)
unnamed: C4.2, R21.2, R25.2, U2.9 (I2P)
unnamed: C10.1, C11.1, U2.13 (REF)
unnamed: C12.2, C13.2, U2.15 (VINTA)
unnamed: R4.2, R43.1, U1.1 (B2)
unnamed: C14.1, R18.2, R24.1, U2.10 (I2N)
unnamed: C15.2, C16.2, U2.3 (VINTD)
unnamed: R13.2, R44.2, U1.3 (B1)
unnamed: R40.1, U$4.2 (EN)
unnamed: C26.2, U$4.3 (COMP)
unnamed: C26.1, R34.2
unnamed: C25.2, D3.N, L1.P$2 (2), U$4.1 (SW)
unnamed: R35.2, R37.1, U$4.4 (FB)
unnamed: Q2.3 (C), R39.1
unnamed: BLUE_LED.K (C), R33.2
unnamed: C25.1, U$4.8 (BST)
unnamed: R9.2, R11.2, U$2.5 (G2)
unnamed: C17.2, R26.2, R28.2, U2.5 (I1P)
unnamed: R41.2, R/G_LED.CX (CG)
unnamed: R42.2, R/G_LED.CR
unnamed: C18.1, R17.1, R27.2, U2.6 (I1N)
unnamed: R10.1, U$1.3 (D2)
unnamed: R10.2, R12.2, U$2.2 (G1)
unnamed: R11.1, U$1.6 (D1)
unnamed: R8.1, U$2.3 (D2), U$2.6 (D1)
unnamed: R39.2, U$5.1 (PIN1)
unnamed: J1.3, R14.2
unnamed: J1.2, R5.1
unnamed: J1.8, R7.1
NRST: C3.2, R5.2, R6.1, U3.3 (EN)
PILOT: D1.N, R3.2, R8.2, U$3.8
PILOT_GEN: R1.2, U3.10 (IO25), U$1.2 (G1), U$1.5 (G2)
PILOT_READ: D2.1 (C), R2.2, R3.1, U3.5 (SENSOR_VN)
RED_LED: R42.1, U3.27 (IO16)
RELAY1: U3.8 (IO32), U$5.2 (PIN2)
RELAY2: U3.9 (IO33), U$5.3 (PIN3)
RELAY_EN: Q2.1 (B), U3.33 (IO21)
RESET_ISO: U2.2 (RESET), U3.14 (IO12)
REVP: U2.20 (/REVP)
RXD0: R7.2, U3.34 (RXD0)
SCL: JP2.2 (PIN2), R45.1, U3.28 (IO17)
SDA: JP2.1 (PIN1), R46.1, U3.29 (IO5)
SPIMISO: U2.26 (MISO), U3.31 (IO19)
SPIMOSI: U2.27 (MOSI), U3.37 (IO23)
SPISCLK: U2.25 (SCLK), U3.30 (IO18)
TXD0: J1.7, U3.35 (TXD0)
V2P: C19.1, R31.1, U2.12 (VP)
ZX: U2.1 (ZX)
ZX_I: U2.21 (ZX_I)

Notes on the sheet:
IO0, IO2, IO5 are bootstrapping pins. DO NOT USE THEM!
MTDI (IO12) and MTDO (IO15) are used for bootstrapping. DO NOT USE THEM!
It is not recommended to use GPIOs 6-11. They are used for SPI Flash (which the WROOM EEPROM Utilizes. Also GPIOs 34-39 are INPUT-ONLY and have no software pull up or pull down pins.
I2C AUX
Mark Pin 1 on the layout for JP2
Label pins on silkscreen
Change to 4-pin header

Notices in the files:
parts and their libraries:
SparkFun-Connectors: Licensing: Creative Commons ShareAlike 4.0 International - https://creativecommons.org/licenses/by-sa/4.0
